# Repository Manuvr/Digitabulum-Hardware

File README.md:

# Digitabulum-Hardware

    .__       ,    .     .
    |  \* _ *-+- _.|_ . .|. .._ _
    |__/|(_]| | (_][_)(_||(_|[ | )
         ._|                      

Hardware source files for Manuvr's motion capture glove.

------------------------

## KiCAD Projects in this repo

### Production Parts

Project | Purpose
:-----|:------
Digitabulum-r2 | Sensor front-end PCB. (Pending release)
r2-Metacarpals | Flex circuit for the metacarpals. (Pending release)
r2-Digit | Flex circuit for digits. (Pending release)
[r2-Backplane](r2-Backplane) | A backplane PCB containing the power-management block and associated support circuits.
[Compute-WROOM32](Compute-WROOM32) | A digitabulum compute PCB based on Espressif's WROOM32 module.

### Hacking and Development Tools

Project | Purpose
:-----|:------
[r2-Dev-Backplane](r2-Dev-Backplane) | A backplane intended for developing CPLD images, Compute PCBs, and power management subsystems.
[PowerPlant-Module](PowerPlant-Module) | Digitabulum's power-management block implemented as a stand-alone breadboard module.
[r2-Adapter](r2-Adapter) | A debugging and development tool. It adapts a Digitabulum board to a standard breadboard. It is also useful as a template for a custom backplane.
[Compute-Template](Compute-Template) | A debugging and development tool. Provides a breakout to the compute/comm PCB connector on an r2-Backplane. It is also useful as a template for a custom Compute PCB.
[SmallTools](SmallTools) | Debugging and development tools.

------------------------

## 3D Models

Blender files for various casings and mocks can be found in the [3DModels](3DModels directory).

------------------------

## License

Manuvr's logo (our trademark) is provided indirectly for the sake of reproducing PCBs of our design, but may not be used on original work without written permission from Manuvr, Inc.

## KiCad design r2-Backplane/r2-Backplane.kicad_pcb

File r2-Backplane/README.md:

# r2-Backplane

This is a backplane PCB for Digitabulum containing the power-management block and associated support circuits.

## Intended usage

This PCB, combined with a Compute board, and a Digitabulum-r2 board (plus sensors) forms a complete electronics package for a single motion-capture glove.

The power-management block of this backplane is broken out in the [PowerPlant-Module](../PowerPlant-Module).

The CPLD GPIO pin has been routed to the 2v5/3v3 selection signal.

## Features
* ESD protection diodes for ingress-resistant USB port.
* Supports full software management of battery.
* Supports reduced-voltage operation and full power down of the sensor package for maximum battery longevity.
* JTAG breakout for in-circuit programming of CPLD.

------------------------

Front | Back
:-------:|:------:
 |

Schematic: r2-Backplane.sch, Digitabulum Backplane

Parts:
C1, C3, C7: 1uF; C_0402_NoSilk; Digikey_Number 490-1320-1-ND
C2: 4.7uF; C_0805; Digikey_Number 490-3335-1-ND
C4, C11: 22uF; C_0805; Digikey_Number 490-1719-1-ND
C5, C10: 10uF; C_0805; Digikey_Number 490-3340-1-ND
C6, C9: 10uF; C_0402_NoSilk; Digikey_Number 490-3340-1-ND
C8: 10nF; C_0402_NoSilk; Digikey_Number 399-1279-1-ND
C12: 0.1uF; C_0402_NoSilk; Digikey_Number 1276-1506-1-ND
CARY1, CARY2, CARY3, CARY4, CARY5: 100nF; CapArray_CKCL44; Digikey_Number 445-1838-1-ND
CON1: USB-MICRO-B; USB_ZX62WRD-B-5PC; Digikey_Number H12192CT-ND
D1: Charge; R_0402_NoSilk; Digikey_Number LNJ347W83RACT-ND
F1: 1A; R_0805_HandSoldering; Digikey_Number NANOSMDC075F-2CT-ND
L1, L2: 2.2uH; L-SMD; Digikey_Number 308-2294-1-ND
L3: 1uH; Neosid_Inductor_SM-NE29_SMD1008; Digikey_Number 490-6699-1-ND
P1: CONN_01X01; ManuvrLogo
P2: CONN_01X02; Pin_Header_Straight_1x02_Pitch2.54mm
P3: CONN_02X16; DF12(3.0)-32DS-0.5V(86); Digikey_Number H11708TR-ND
P4: HiRose-02X15; DF12(4.0)-30DS-0.5V(86); Digikey_Num H5238CT-ND
P6: DEBUG; Pin_Header_Straight_1x08_Pitch1.27mm
QA_NPN1: QA_NPN; SOT-363_SC-70-6_Handsoldering; Digikey_Number NC7SV57P6XCT-ND
R1, R3: 1k; R_0402_NoSilk; Digikey_Number P1.00KLCT-ND
R4: 68mOhm; R_2512; Digikey_Number CSRN2512FK68L0CT-ND
RP1: 22; RES_4_EXBN8V; Digikey_Number Y10220CT-ND
RP2: 1k; RES_4_EXBN8V; Digikey_Number Y9102CT-ND
U1, U2, U3, U4: LSF0204x; R-PUQFN-N12; Digikey_Number 296-40404-1-ND
U5: LTC2942-1; DFN-6-1EP_2x3mm_Pitch0.5mm; Digikey_Number LTC2942CDCB-1#TRMPBFCT-ND
U6: BQ24155; Digikey_Number 296-27187-1-ND
U7: SC283; MLPQ-W18 (2mmx3mm); Digikey_Number SC283WLCT-ND
U8: EMIF02-USB03F2; FCBGA12; Digikey_Number 497-13521-1-ND

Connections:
/ALERT: P4.30, U5.5
/CHIP_PU: P4.15, P6.2
/CPLD_EXT_CLK: P3.31, U3.4
/CPLD_GPIO_0: P3.21, QA_NPN1.6
/CPLD_OE: P3.26, U3.5
/I2C_SCL: P4.4, U4.9, U5.3, U6.2
/I2C_SCL_LV: P3.15, RP2.4 (R4.1), U4.3
/I2C_SDA: P4.5, U4.8, U5.4, U6.3
/I2C_SDA_LV: P3.14, RP2.3 (R3.1), U4.4
/IRQ_WAKEUP: P3.17, U2.5
/ISEL: P4.6, U6.5
/PIN_0: P4.14, P6.3
/SPI1_CLK: P3.20, U2.2
/SPI1_CS_0: P3.32, U3.3
/SPI1_MISO: P3.18, U2.4
/SPI1_MOSI: P3.19, U2.3
/SPI2_CLK: P3.24, U1.3
/SPI2_CS: P3.23, U1.4
/SPI2_MOSI: P3.22, U1.5
/TCK: P3.28, P6.5, R1.2
/TDI: P3.30, P6.7
/TDO: P3.29, P6.6
/TMS: P3.27, P6.4
/USB_D+: P4.2, RP1.7 (R2.2), U8.C3
/USB_D-: P4.1, RP1.8 (R1.2), U8.D3
/VCC0: C4.1, CARY1.5, CARY1.7, CARY2.5, CARY2.7, CARY3.5, CARY3.7, CARY4.5, CARY4.7, CARY5.1, CARY5.3, CARY5.5, CARY5.7, L1.1, P4.10, P4.11, QA_NPN1.3, QA_NPN1.5, U1.11, U2.11, U3.11, U4.11, U7.18
/VCC1: C11.1, CARY1.1, CARY1.3, CARY2.1, CARY2.3, CARY3.1, CARY3.3, CARY4.1, CARY4.3, L2.2, P3.6, P3.7, P6.8, RP2.5 (R4.2), RP2.6 (R3.2), RP2.7 (R2.2), RP2.8 (R1.2), U1.1, U2.1, U3.1, U4.1, U7.9
/VCCUSB: C1.1, C6.1, CON1.1, P4.7, R3.2, U6.14, U8.B3
/Vbatt: C5.1, C7.1, C9.1, C10.1, P3.9, P3.10, R4.1, U5.1, U6.6, U6.7, U7.1, U7.10, U7.14, U7.15, U7.16, U7.17
/Vlipo: F1.2, U5.6
/~CPLD_RESET: P3.25, U1.2
/~LED_INT: P3.13, RP2.1 (R1.1), U4.5
/~LED_RESET: P3.16, U4.2
/~REQ: P3.12, U3.2
/~SHUTDOWN: P4.13, QA_NPN1.1, U1.12, U2.12, U3.12, U4.12, U7.5, U7.7, U7.8
GND: C1.2, C2.2, C3.2, C4.2, C5.2, C6.2, C7.2, C9.2, C10.2, C11.2, C12.2, CARY1.2, CARY1.4, CARY1.6, CARY1.8, CARY2.2, CARY2.4, CARY2.6, CARY2.8, CARY3.2, CARY3.4, CARY3.6, CARY3.8, CARY4.2, CARY4.4, CARY4.6, CARY4.8, CARY5.2, CARY5.4, CARY5.6, CARY5.8, CON1.5, CON1.G0, CON1.G1, CON1.G2, CON1.G3, CON1.G4, CON1.G5, CON1.G6, P1.1, P2.1, P3.1, P3.2, P3.3, P3.4, P3.N0, P3.N1, P4.3, P4.8, P4.9, P4.12, P4.N0, P4.N1, P6.1, QA_NPN1.2, R1.1, RP1.3 (R3.1), RP1.4 (R4.1), RP1.5 (R4.2), RP1.6 (R3.2), U1.6, U2.6, U3.6, U4.6, U5.2, U6.0, U6.10, U6.11, U7.3, U7.4, U7.12, U7.13, U7.T1, U7.T2, U8.A2, U8.D2
unnamed: C2.1, U6.13
unnamed: C3.1, U6.8
unnamed: C8.1, L3.1, U6.12
unnamed: C8.2, U6.1
unnamed: C12.1, L3.2, R4.2, U6.9
unnamed: CON1.2, RP1.1 (R1.1), U8.D1
unnamed: CON1.3, RP1.2 (R2.1), U8.C1
unnamed: CON1.4, U8.A3
unnamed: D1.1 (K), U6.4
unnamed: D1.2 (A), R3.1
unnamed: F1.1, P2.2
unnamed: L1.2, U7.2
unnamed: L2.1, U7.11
unnamed: P4.16, U2.7
unnamed: P4.17, U2.8
unnamed: P4.18, U2.9
unnamed: P4.19, U2.10
unnamed: P4.20, U1.7
unnamed: P4.21, U1.8
unnamed: P4.22, U1.9
unnamed: P4.23, U1.10
unnamed: P4.24, U3.7
unnamed: P4.25, U3.8
unnamed: P4.26, U3.9
unnamed: P4.27, U3.10
unnamed: P4.28, U4.7
unnamed: P4.29, U4.10
unnamed: QA_NPN1.4, U7.6

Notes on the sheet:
We will use these CPLD faculties for power control.
NOTE: This is actually an NC7SV57. The pins and footprint are correct.
NOTE: This design assumes that the system half of the voltage regulator is always running at 3.3v.

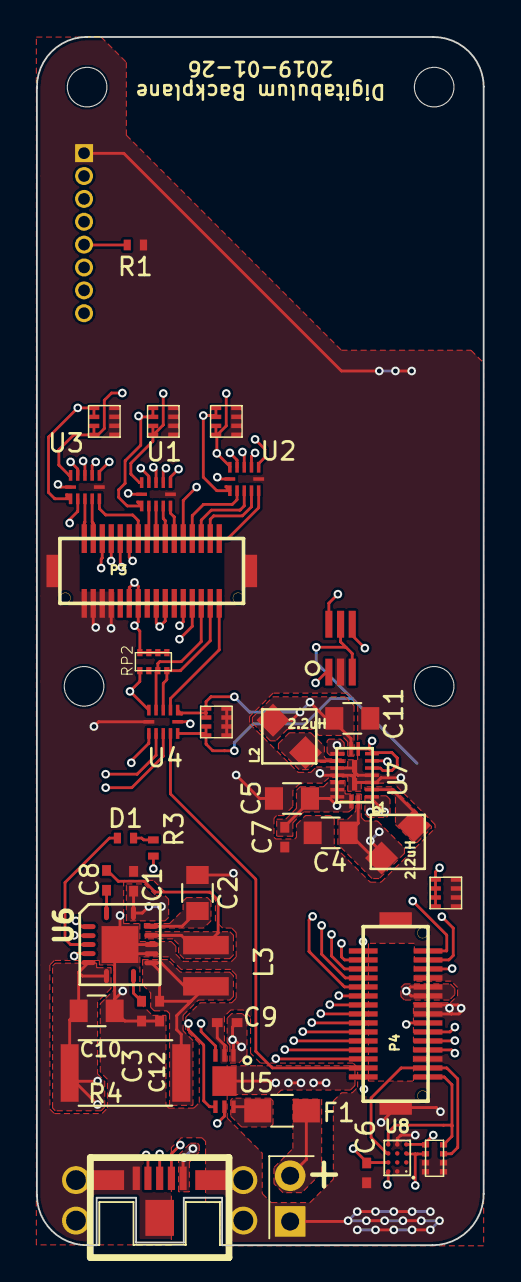
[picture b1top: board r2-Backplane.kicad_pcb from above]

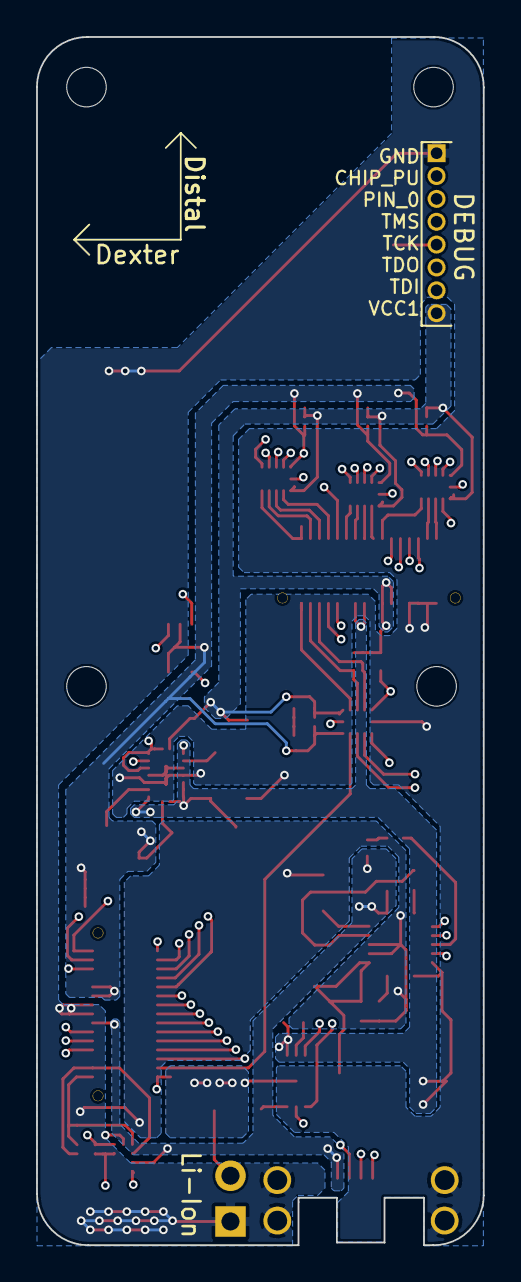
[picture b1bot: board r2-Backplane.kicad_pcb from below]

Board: 4 copper layers, 24.8 x 67.1 mm, 47 parts (2 on the bottom side), 64 nets.

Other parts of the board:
MH0: MH0; MountingHole_2.2mm_M2_DIN965
MH1: MH1; MountingHole_2.2mm_M2_DIN965
MH2, MH3: MountingHole_2.2mm_M2_DIN965
P1#2: CONN_01X01; ManuvrLogo

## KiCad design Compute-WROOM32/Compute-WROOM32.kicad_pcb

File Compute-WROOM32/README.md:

# Compute-WROOM32

This is one possible compute PCB to be used with Digitabulum-r2.

## Intended usage

This PCB, combined with a [backplane](../r2-Backplane), and a Digitabulum-r2 board (plus sensors) forms a complete electronics package for a single motion-capture glove.

## Features

* Integrated USB<-->Serial converter with Espressif monitor reset support.

## Attribution
This project uses [adamjvr's KiCAD library for the ESP32](https://github.com/adamjvr/ESP32-kiCAD-Footprints).

------------------------

Front | Back
:-------:|:------:
 |

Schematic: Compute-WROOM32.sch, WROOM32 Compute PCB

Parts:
C1: 10nF; C_0402_NoSilk; Digikey_Number 399-1279-1-ND
C2: 100uF; C_0805; Digikey_Number 478-8393-1-ND
C3: 4.7uF; C_0402_NoSilk; Digikey_Number 445-5947-1-ND
C5, C6: 0.1uF; C_0402_NoSilk; Digikey_Number 1276-1506-1-ND
CARY1, CARY3: 100nF; CapArray_CKCL44; Digikey_Number 445-1838-1-ND
CARY4: 22pF; CapArray_CKCL44; Digikey_Number 445-1824-1-ND
P1: HiRose-02X15; DF12(4.0)-30DS-0.5V(86); Digikey_Number H5215CT-ND
P4: CONN_01X01; ManuvrLogo
QA_NPN1: QA_NPN; TSOT-23-6_MK06A_HandSoldering; Digikey_Number 1727-5166-1-ND
RP1: 15k; RES_4_EXBN8V; Digikey_Number Y10153CT-ND
RP2: 15k; RES_4_EXBN8V; Digikey_Number Y9102CT-ND
U1: ESP32-WROOM_U; ESP32-WROOM-U; Digikey_Number 1904-1028-1-ND
U2: FT231XS; LFCSP_WQ20; Digikey_Number 768-1128-1-ND
U3: ASTMLP; ASTMLPD; Digikey_Number ‎535-13087-1-ND‎

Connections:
/ALERT: P1.1, U1.33
/CHIP_PU: CARY3.4, P1.16, QA_NPN1.6, RP1.6 (R3), U1.3
/CPLD_EXT_CLK: P1.6, U3.3
/CPLD_OE: P1.7, U1.26
/FTDI_RESET: C6.1, U1.36, U2.10, U2.11, U2.20
/I2C_SCL: P1.27, RP2.5 (R4), U1.12
/I2C_SDA: P1.26, RP2.6 (R3), U1.11
/IRQ_WAKEUP: P1.15, U1.8
/ISEL: P1.25, U1.37
/PIN_0: CARY3.2, P1.17, QA_NPN1.3, RP1.5 (R4), U1.25
/RxD: U1.35, U2.1
/SPI1_CLK: P1.12, U1.16
/SPI1_CS: P1.5, U1.28
/SPI1_MISO: P1.14, U1.10
/SPI1_MOSI: P1.13, U1.13
/SPI2_CLK: P1.9, U1.6
/SPI2_CS: P1.10, U1.7
/SPI2_MOSI: P1.11, U1.9
/TxD: U1.34, U2.17
/USB_D+: CARY4.2, CARY4.4, P1.29, U2.8
/USB_D-: CARY4.6, CARY4.8, P1.30, U2.9
/VCC0: C2.1, CARY1.1, CARY1.3, CARY1.5, CARY1.7, CARY3.6, CARY3.8, P1.20, P1.21, RP1.1, RP1.2, RP1.3, RP1.4, RP2.1, RP2.2, RP2.3, RP2.4, U1.2, U3.4
/VCCUSB: C1.1, C3.1, C5.1, P1.24, U2.12
/~CPLD_RESET: P1.8, U1.24
/~LED_INT: P1.3, U1.31
/~LED_RESET: P1.2, U1.29
/~REQ: P1.4, U1.30
/~SHUTDOWN: P1.18, U1.14
GND: C1.2, C2.2, C3.2, C5.2, C6.2, CARY1.2, CARY1.4, CARY1.6, CARY1.8, CARY3.1, CARY3.3, CARY3.5, CARY3.7, CARY4.1, CARY4.3, CARY4.5, CARY4.7, P1.19, P1.22, P1.23, P1.28, P1.N0, P1.N1, P4.1, U1.1, U1.15, U1.38, U1.39, U2.3, U2.13, U2.21, U3.2
unnamed: QA_NPN1.1, QA_NPN1.5, U2.19
unnamed: QA_NPN1.2, QA_NPN1.4, U2.18
unnamed: U1.27, U3.1

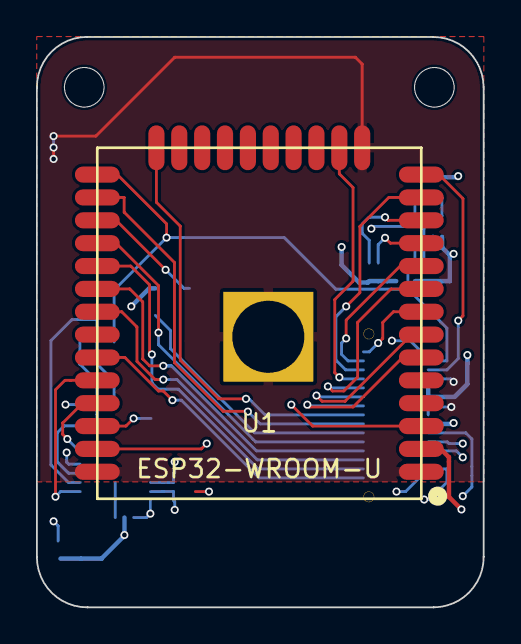
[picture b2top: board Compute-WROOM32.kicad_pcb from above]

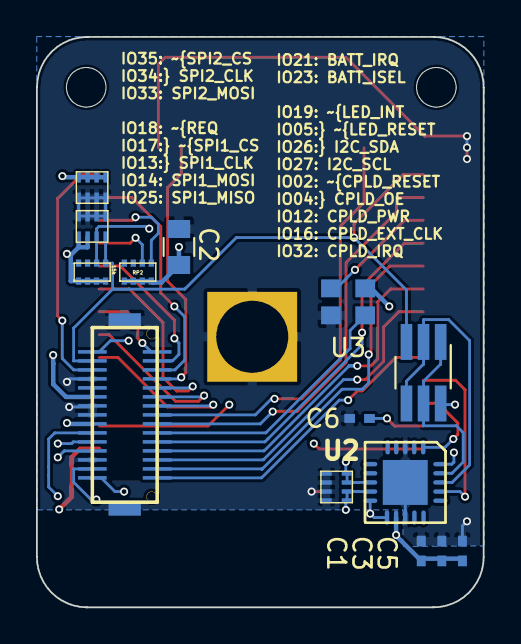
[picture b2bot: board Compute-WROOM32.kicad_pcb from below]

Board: 4 copper layers, 24.8 x 31.7 mm, 17 parts (14 on the bottom side), 32 nets.

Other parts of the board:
mh0, mh1: MountingHole_2.2mm_M2_DIN965

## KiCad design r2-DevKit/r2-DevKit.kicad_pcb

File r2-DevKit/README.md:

# r2-DevKit

This is a backplane PCB for Digitabulum. When combined with the [PowerPlant](../PowerPlant-Module), it has the same schematic as the [r2-Backplane](../r2-Backplane).

## Intended usage

This board is intended as a testing harness for functional subunits designed for use with the Digitabulum sensor package. This would be the board you would want for prototyping new CPLD designs, power supplies, or compute modules.

If you do not want to do those things, but just want a working glove, you should use the [r2-Backplane](../r2-Backplane) instead.

The CPLD GPIO pin has been routed to the 2v5/3v3 selection signal.

## Features
* ESD protection diodes for ingress-resistant USB port.
* Supports full software management of battery.
* Supports reduced-voltage operation and full power down of the sensor package for maximum battery longevity.
* JTAG breakout for in-circuit programming of CPLD.

------------------------

Front | Back
:-------:|:------:
 |

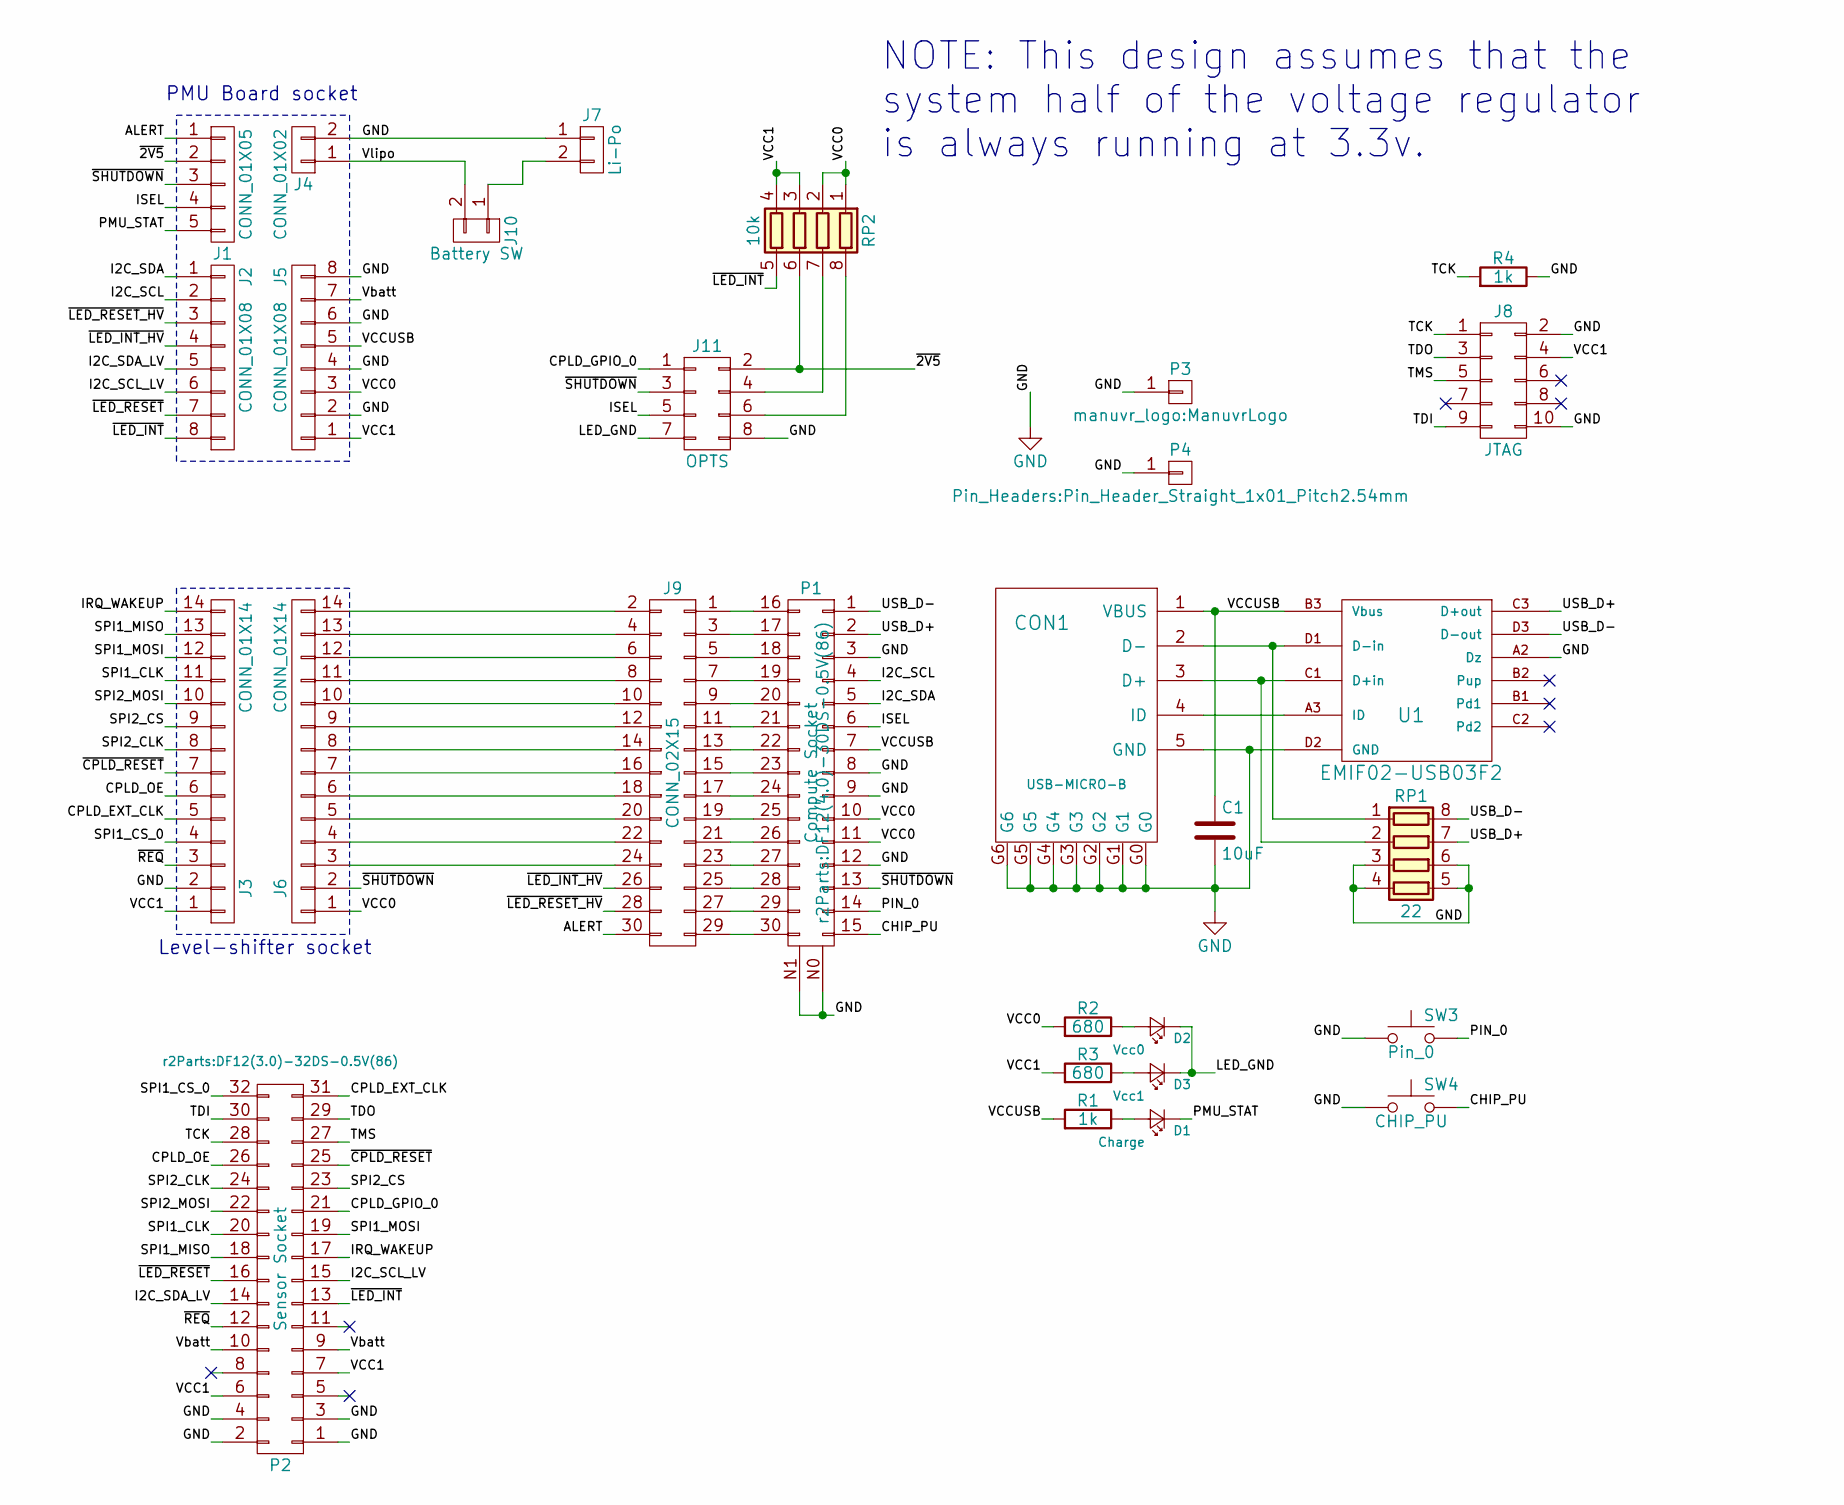
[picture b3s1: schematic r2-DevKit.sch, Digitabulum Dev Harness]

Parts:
C1: 10uF; C_0402_NoSilk; Digikey_Number 490-3340-1-ND
CON1: USB-MICRO-B; USB_ZX62WRD-B-5PC; Digikey_Number H12192CT-ND
D1: Charge; D_0603; Digikey_Number 732-4971-1-ND
D2: Vcc0; D_0603; Digikey_Number 732-4971-1-ND
D3: Vcc1; D_0603; Digikey_Number 732-4971-1-ND
J1: CONN_01X05; Pin_Header_Straight_1x05_Pitch2.54mm
J2, J5: CONN_01X08; Pin_Header_Straight_1x08_Pitch2.54mm
J3, J6: CONN_01X14; Pin_Header_Straight_1x14_Pitch2.54mm
J4: CONN_01X02; Pin_Header_Straight_1x02_Pitch2.54mm
J7: Li-Po; JST-Battery-Right-Angle; Digikey_Number 455-1749-6-ND
J8: JTAG; IDC_Header_Straight_10pins
J9: CONN_02X15; Pin_Header_Straight_2x15_Pitch2.54mm
J10: Battery SW; Pin_Header_Straight_1x02_Pitch2.54mm
J11: OPTS; Pin_Header_Straight_2x04_Pitch2.54mm
P1: Compute Socket; DF12(4.0)-30DS-0.5V(86); Digikey_Num H5238CT-ND
P2: Sensor Socket; DF12(3.0)-32DS-0.5V(86); Digikey_Number H11708TR-ND
P3: CONN_01X01; ManuvrLogo
P4: CONN_01X01; Pin_Header_Straight_1x01_Pitch2.54mm
R1, R4: 1k; R_0402_NoSilk; Digikey_Number 311-1.0KJRCT-ND
R2, R3: 680; R_0402_NoSilk; Digikey_Number 311-680JRCT-ND
RP1: 22; RES_4_EXBN8V; Digikey_Number Y10220CT-ND
RP2: 10k; RES_4_EXBN8V; Digikey_Number Y10220CT-ND
SW3: Pin_0; SW_SPST_Panasonic_EVQPL_3PL_5PL_PT_A15
SW4: CHIP_PU; SW_SPST_Panasonic_EVQPL_3PL_5PL_PT_A15
U1: EMIF02-USB03F2; FCBGA12; Digikey_Number 497-13521-1-ND

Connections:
/ALERT: J1.1, J9.30
/CHIP_PU: P1.15, SW4.2
/CPLD_EXT_CLK: J3.5, P2.31
/CPLD_GPIO_0: J11.1, P2.21
/CPLD_OE: J3.6, P2.26
/I2C_SCL: J2.2, P1.4
/I2C_SCL_LV: J2.6, P2.15
/I2C_SDA: J2.1, P1.5
/I2C_SDA_LV: J2.5, P2.14
/IRQ_WAKEUP: J3.14, P2.17
/ISEL: J1.4, J11.5, P1.6
/LED_GND: D2.1 (K), D3.1 (K), J11.7
/PIN_0: P1.14, SW3.2
/PMU_STAT: D1.1 (K), J1.5
/SPI1_CLK: J3.11, P2.20
/SPI1_CS_0: J3.4, P2.32
/SPI1_MISO: J3.13, P2.18
/SPI1_MOSI: J3.12, P2.19
/SPI2_CLK: J3.8, P2.24
/SPI2_CS: J3.9, P2.23
/SPI2_MOSI: J3.10, P2.22
/TCK: J8.1, P2.28, R4.2
/TDI: J8.9, P2.30
/TDO: J8.3, P2.29
/TMS: J8.5, P2.27
/USB_D+: P1.2, RP1.7 (R2.2), U1.C3 (D+out)
/USB_D-: P1.1, RP1.8 (R1.2), U1.D3 (D-out)
/VCC0: J5.3, J6.1, P1.10, P1.11, R2.2, RP2.1 (R1.1), RP2.2 (R2.1)
/VCC1: J3.1, J5.1, J8.4, P2.6, P2.7, R3.2, RP2.3 (R3.1), RP2.4 (R4.1)
/VCCUSB: C1.1, CON1.1 (VBUS), J5.5, P1.7, R1.2, U1.B3 (Vbus)
/Vbatt: J5.7, P2.9, P2.10
/Vlipo: J4.1, J10.2
/~2V5: J1.2, J11.2, RP2.6 (R3.2)
/~CPLD_RESET: J3.7, P2.25
/~LED_INT: J2.8, P2.13, RP2.5 (R4.2)
/~LED_INT_HV: J2.4, J9.26
/~LED_RESET: J2.7, P2.16
/~LED_RESET_HV: J2.3, J9.28
/~REQ: J3.3, P2.12
/~SHUTDOWN: J1.3, J6.2, J11.3, P1.13
GND: C1.2, CON1.5 (GND), CON1.G0, CON1.G1, CON1.G2, CON1.G3, CON1.G4, CON1.G5, CON1.G6, J3.2, J4.2, J5.2, J5.4, J5.6, J5.8, J7.1, J8.2, J8.10, J11.8, P1.3, P1.8, P1.9, P1.12, P1.N0, P1.N1, P2.1, P2.2, P2.3, P2.4, P3.1, P4.1, R4.1, RP1.3 (R3.1), RP1.4 (R4.1), RP1.5 (R4.2), RP1.6 (R3.2), SW3.1, SW4.1, U1.A2 (Dz), U1.D2 (GND)
unnamed: CON1.2 (D-), RP1.1 (R1.1), U1.D1 (D-in)
unnamed: CON1.3 (D+), RP1.2 (R2.1), U1.C1 (D+in)
unnamed: CON1.4 (ID), U1.A3 (ID)
unnamed: D1.2 (A), R1.1
unnamed: D2.2 (A), R2.1
unnamed: D3.2 (A), R3.1
unnamed: J6.3, J9.24
unnamed: J6.4, J9.22
unnamed: J6.5, J9.20
unnamed: J6.6, J9.18
unnamed: J6.7, J9.16
unnamed: J6.8, J9.14
unnamed: J6.9, J9.12
unnamed: J6.10, J9.10
unnamed: J6.11, J9.8
unnamed: J6.12, J9.6
unnamed: J6.13, J9.4
unnamed: J6.14, J9.2
unnamed: J9.1, P1.16
unnamed: J9.3, P1.17
unnamed: J9.5, P1.18
unnamed: J9.7, P1.19
unnamed: J9.9, P1.20
unnamed: J9.11, P1.21
unnamed: J9.13, P1.22
unnamed: J9.15, P1.23
unnamed: J9.17, P1.24
unnamed: J9.19, P1.25
unnamed: J9.21, P1.26
unnamed: J9.23, P1.27
unnamed: J9.25, P1.28
unnamed: J9.27, P1.29
unnamed: J9.29, P1.30
unnamed: J7.2, J10.1
unnamed: J11.4, RP2.7 (R2.2)
unnamed: J11.6, RP2.8 (R1.2)

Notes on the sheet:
PMU Board socket
Level-shifter socket
NOTE: This design assumes that the system half of the voltage regulator is always running at 3.3v.

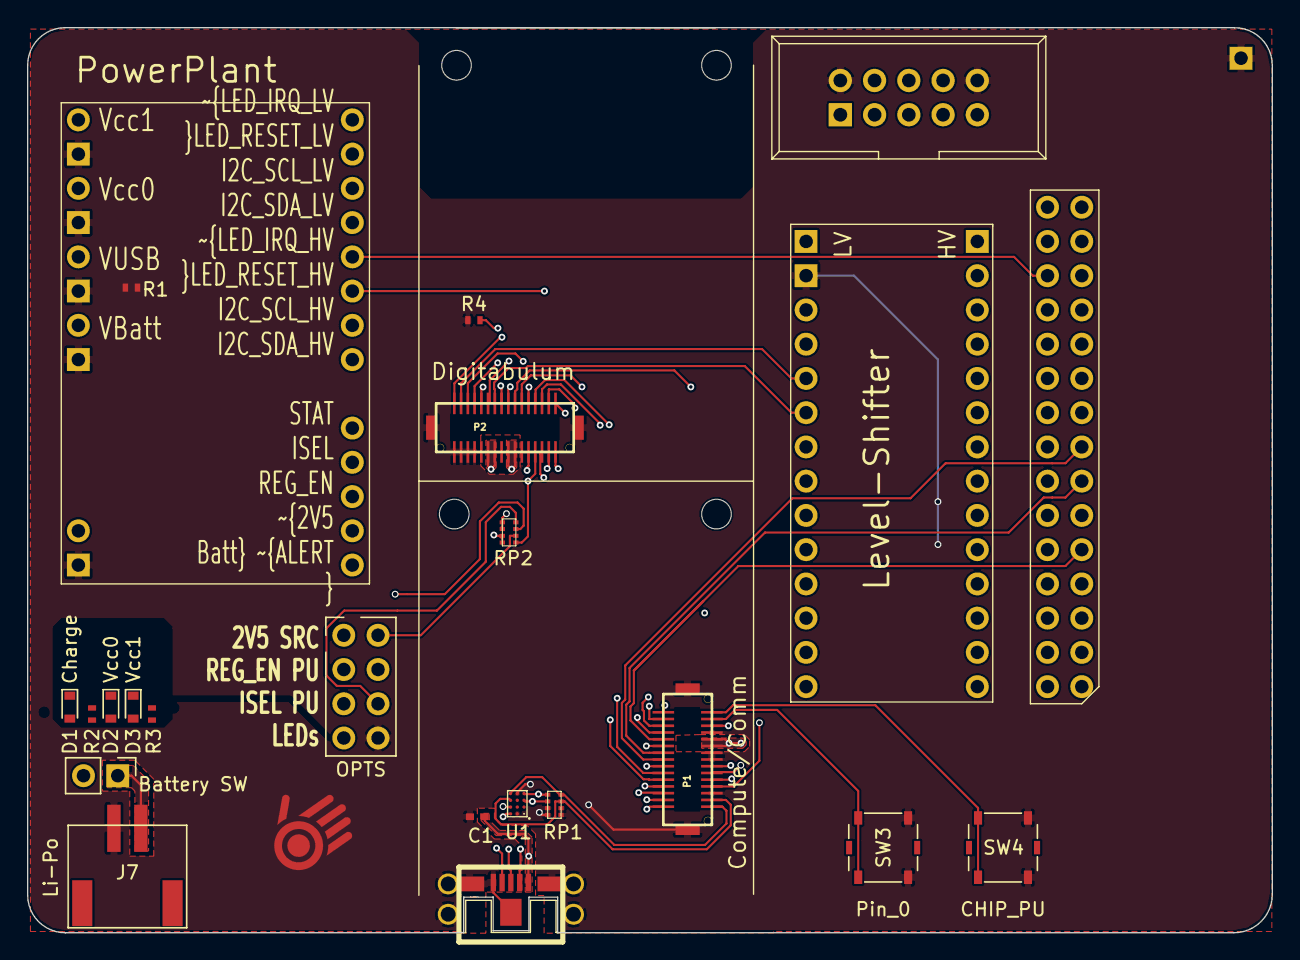
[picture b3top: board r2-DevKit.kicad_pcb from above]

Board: 4 copper layers, 92.3 x 67.1 mm, 33 parts (0 on the bottom side), 77 nets.

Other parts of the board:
MH0: MH0; MountingHole_2.2mm_M2_DIN965
MH1: MH1; MountingHole_2.2mm_M2_DIN965
MH2, MH3: MountingHole_2.2mm_M2_DIN965

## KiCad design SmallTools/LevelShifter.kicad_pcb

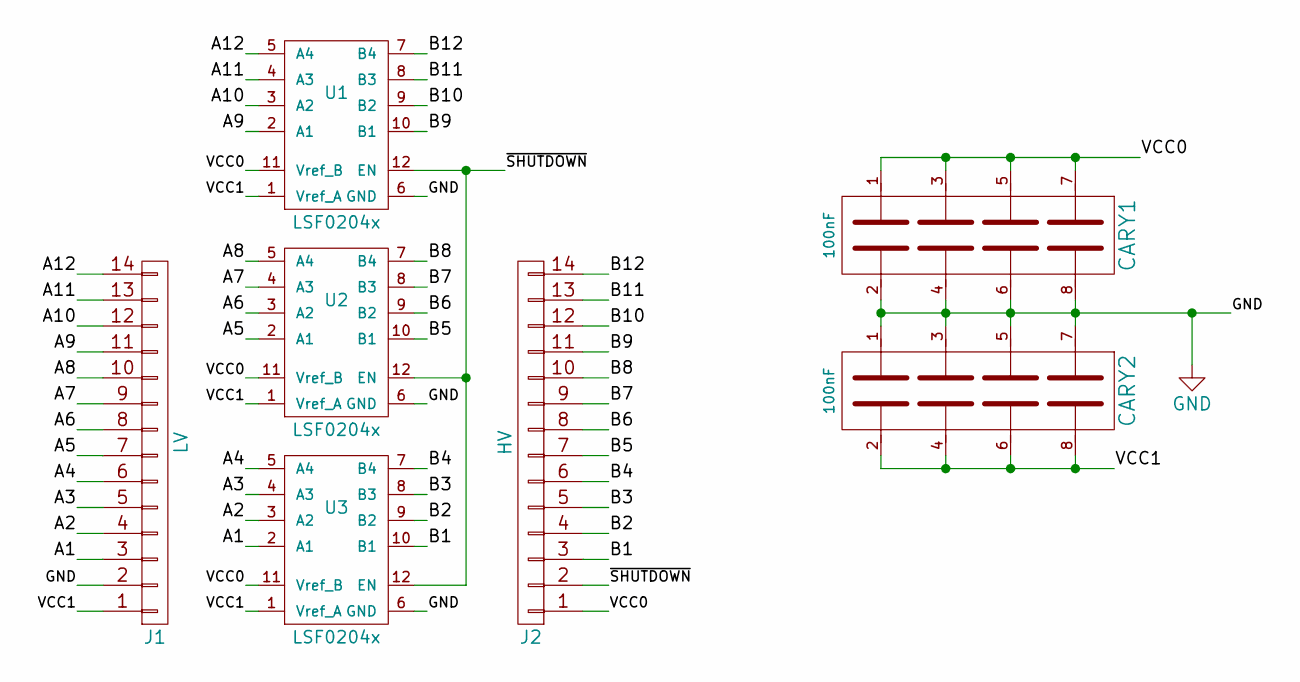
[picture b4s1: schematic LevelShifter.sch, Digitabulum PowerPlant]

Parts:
CARY1, CARY2: 100nF; CapArray_CKCL44; Digikey_Number 445-1838-1-ND
J1: LV; Pin_Header_Straight_1x14_Pitch2.54mm
J2: HV; Pin_Header_Straight_1x14_Pitch2.54mm
U1, U2, U3: LSF0204x; R-PUQFN-N12

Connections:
/A1: J1.3, U3.2 (A1)
/A2: J1.4, U3.3 (A2)
/A3: J1.5, U3.4 (A3)
/A4: J1.6, U3.5 (A4)
/A5: J1.7, U2.2 (A1)
/A6: J1.8, U2.3 (A2)
/A7: J1.9, U2.4 (A3)
/A8: J1.10, U2.5 (A4)
/A9: J1.11, U1.2 (A1)
/A10: J1.12, U1.3 (A2)
/A11: J1.13, U1.4 (A3)
/A12: J1.14, U1.5 (A4)
/B1: J2.3, U3.10 (B1)
/B2: J2.4, U3.9 (B2)
/B3: J2.5, U3.8 (B3)
/B4: J2.6, U3.7 (B4)
/B5: J2.7, U2.10 (B1)
/B6: J2.8, U2.9 (B2)
/B7: J2.9, U2.8 (B3)
/B8: J2.10, U2.7 (B4)
/B9: J2.11, U1.10 (B1)
/B10: J2.12, U1.9 (B2)
/B11: J2.13, U1.8 (B3)
/B12: J2.14, U1.7 (B4)
/VCC0: CARY1.1, CARY1.3, CARY1.5, CARY1.7, J2.1, U1.11 (Vref_B), U2.11 (Vref_B), U3.11 (Vref_B)
/VCC1: CARY2.2, CARY2.4, CARY2.6, CARY2.8, J1.1, U1.1 (Vref_A), U2.1 (Vref_A), U3.1 (Vref_A)
/~SHUTDOWN: J2.2, U1.12 (EN), U2.12 (EN), U3.12 (EN)
GND: CARY1.2, CARY1.4, CARY1.6, CARY1.8, CARY2.1, CARY2.3, CARY2.5, CARY2.7, J1.2, U1.6 (GND), U2.6 (GND), U3.6 (GND)

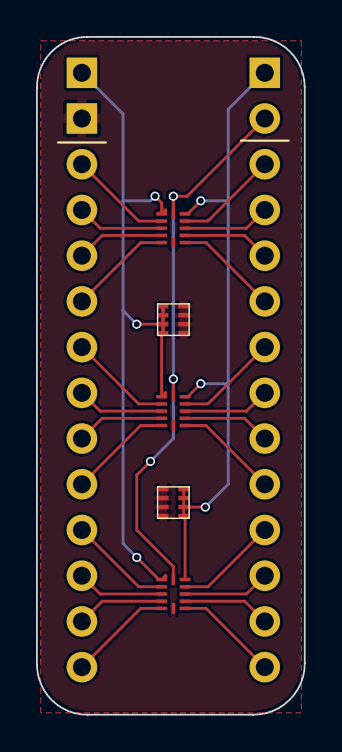
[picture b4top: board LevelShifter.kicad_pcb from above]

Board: 4 copper layers, 14.9 x 37.7 mm, 7 parts (0 on the bottom side), 28 nets.

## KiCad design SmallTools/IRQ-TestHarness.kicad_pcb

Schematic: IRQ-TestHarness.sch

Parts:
CARY1: CAPARRAY_4; CapArray_CKCL44
P1: CONN_01X05; Pin_Header_Straight_1x05_Pitch2.54mm
P2: CONN_01X05; Pin_Header_Straight_1x05_Pitch1.27mm
RP1, RP2, RP3, RP5: R_PACK4; RES_4_EXBN8V
RP4: R_PACK4; SW_DIP_x4_W5.08mm_Slide_Copal_CHS-A
SW1, SW2, SW3, SW4, SW5, SW6, SW7, SW8, SW9, SW10, SW11, SW12: SW_PUSH_SMALL_H; SW_SPST_Panasonic_EVQPL_3PL_5PL_PT_A15
U2, U3: 74HC165; DHVQFN16-3.5x2.5; Digikey_Number 568-7724-1-ND

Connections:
/GND: CARY1.2, CARY1.4, CARY1.6, CARY1.8, P1.1, P2.1, RP1.5, RP1.6, RP1.7, RP1.8, RP2.5, RP2.6, RP2.7, RP2.8, RP3.5, RP3.6, RP3.7, RP3.8, RP5.1, RP5.2, RP5.3, RP5.4, U2.0, U2.8, U2.10, U2.15, U3.0, U3.8, U3.15
/INT_0_0: RP3.1, SW9.1, U3.3
/INT_0_1: RP2.1, SW5.1, U2.3
/INT_0_2: RP1.4, SW4.1, U2.14
/INT_1_0: RP3.2, SW10.1, U3.4
/INT_1_1: RP2.2, SW6.1, U2.4
/INT_1_2: RP1.3, SW3.1, U2.13
/INT_2_0: RP3.3, SW11.1, U3.5
/INT_2_1: RP2.3, SW7.1, U2.5
/INT_2_2: RP1.2, SW2.1, U2.12
/INT_3_0: RP3.4, SW12.1, U3.6
/INT_3_1: RP2.4, SW8.1, U2.6
/INT_3_2: RP1.1, SW1.1, U2.11
/IRQ_CLK: P1.2, P2.2, U2.2, U3.2
/IRQ_DAT: P1.4, P2.4, U3.9
/IRQ_LOAD: P1.3, P2.3, U2.1, U3.1
/VCC: CARY1.1, CARY1.3, CARY1.5, CARY1.7, P1.5, P2.5, RP4.1, RP4.2, RP4.3, RP4.4, SW1.2, SW2.2, SW3.2, SW4.2, SW5.2, SW6.2, SW7.2, SW8.2, SW9.2, SW10.2, SW11.2, SW12.2, U2.16, U3.16
unnamed: RP4.5, RP5.8, U3.11
unnamed: RP4.6, RP5.7, U3.12
unnamed: RP4.7, RP5.6, U3.13
unnamed: RP4.8, RP5.5, U3.14
unnamed: U2.9, U3.10

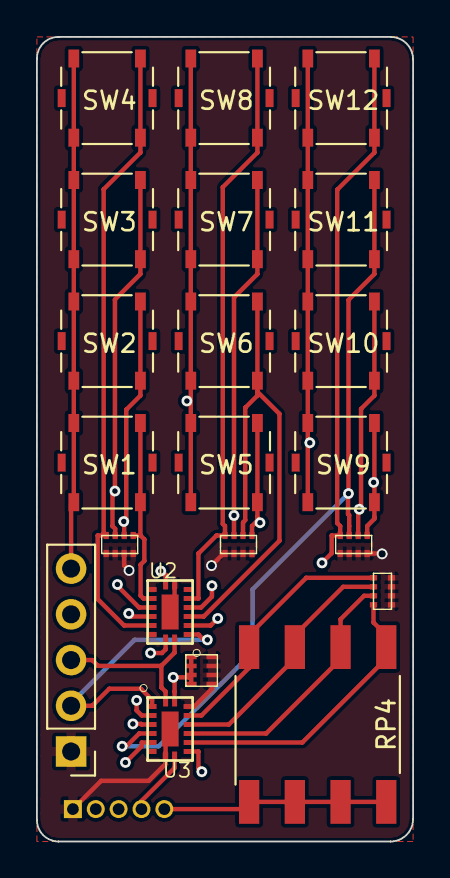
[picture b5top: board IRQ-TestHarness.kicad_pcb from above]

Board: 4 copper layers, 20.9 x 44.7 mm, 22 parts (0 on the bottom side), 22 nets.

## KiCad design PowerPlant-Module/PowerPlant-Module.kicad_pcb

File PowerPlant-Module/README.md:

# Digitabulum-PowerPlant

This is the power-management block of Manuvr's motion-capture glove. It has been broken out as a module for testing and re-use.

## Intended usage
A software-mediated single-cell li-ion battery manager for cases needing bursts of a few watts and supporting long periods of quiescent standby.

## Features
* Dual output
* Secondary regulator has three voltages (0, 2.5, 3.3), and can be changed dynamically.
* Fused battery (resetable)
* Charger and fuel gauge are both i2c
* Integrated 4-bit level-shifter (i2c capable)
* Accepts up to 20v input
* 2.54 headers
* Single-sided assembly for easy thermal-relief

## Primary components

Feature | Manufacturer | Part
:----|-----:|:----
Battery charger | TI | BQ24155
Fuel gauge | Linear | LTC2942-1
Regulator | SEMTECH | SC283
Level-shifter | TI | LSF0204

## Constraints
* Battery must be li-ion chemistry.
* Primary regulator is always on and fixed at a 3.3v output.
* No single regulator may provide more than 1.8A, and the module's maximum output wattage is 4.2 watts. See below.

Charge and discharge rate on the battery must not exceed 1A, or the internal sense resistor in the fuel gauge will burn out. There is a resetable fuse to prevent damage, but this forms the limit on the module's practical output rating. However, the charger IC can handle up to a 20v input, and could conceivably draw more than the module's maximum output from the input source as it charges and powers the load. Fuse accordingly. :-)

------------------------

Front | Back
:-------:|:------:
  |

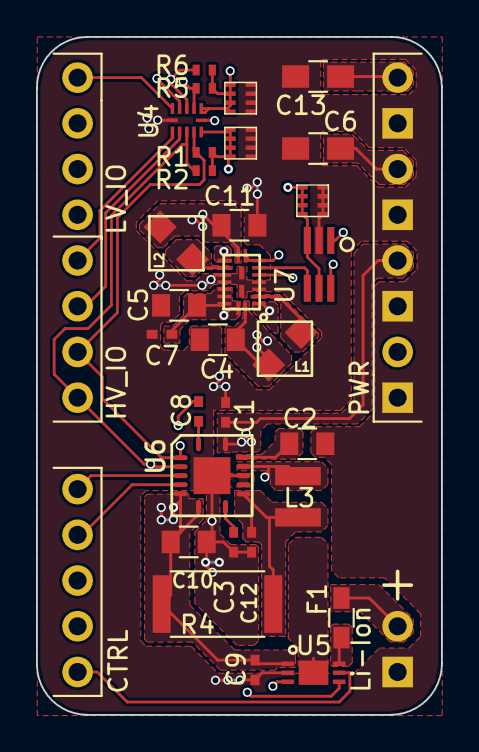
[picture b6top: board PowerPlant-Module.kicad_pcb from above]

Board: 4 copper layers, 22.5 x 37.7 mm, 35 parts (0 on the bottom side), 28 nets.

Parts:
C1, C3, C7: 1uF; C_0402_NoSilk
C2: 4.7uF; C_0805
C4, C11: 22uF; C_0805
C5, C10: 10uF; C_0805
C6, C13: 100uF; C_0805_HandSoldering
C8: 10nF; C_0402_NoSilk
C9: 10uF; C_0402_NoSilk
C12: 0.1uF; C_0402_NoSilk
CARY1, CARY2, CARY3: 100nF; CapArray_CKCL44
F1: F_Small; R_0603_HandSoldering
L1, L2: 2.2uH; L-SMD
L3: 1uH; Neosid_Inductor_SM-NE29_SMD1008
P2: CONN_01X02; Pin_Header_Straight_1x02_Pitch2.54mm
P3: PWR; Pin_Header_Straight_1x08_Pitch2.54mm
P4: CTRL; Pin_Header_Straight_1x05_Pitch2.54mm
P5: LV_IO; Pin_Header_Straight_1x04_Pitch2.54mm
P6: HV_IO; Pin_Header_Straight_1x04_Pitch2.54mm
QA_NPN1: QA_NPN; SOT-363_SC-70-6_Handsoldering
R1, R2, R5, R6: 1k; R_0402_NoSilk
R4: 68mOhm; R_2512
U4: LSF0204x; R-PUQFN-N12
U5: LTC2942-1; DFN-6-1EP_2x3mm_Pitch0.5mm
U6: BQ24155
U7: SC283; MLPQ-W18 (2mmx3mm)

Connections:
/ALERT: P4.5, U5.5
/I2C_SCL: P6.3, R1.1, U4.10, U5.3, U6.2
/I2C_SCL_LV: P5.3, R5.1, U4.2
/I2C_SDA: P6.4, R2.1, U4.9, U5.4, U6.3
/I2C_SDA_LV: P5.4, R6.1, U4.3
/IO_0: P6.1, U4.7
/IO_1: P6.2, U4.8
/ISEL: P4.2, U6.5
/LV_IO_0: P5.1, U4.5
/LV_IO_1: P5.2, U4.4
/STAT: P4.1, U6.4
/VCC0: C4.1, C6.1, CARY1.1, CARY1.3, CARY1.5, CARY1.7, CARY3.1, CARY3.3, CARY3.5, CARY3.7, L1.1, P3.6, QA_NPN1.3, QA_NPN1.5, R1.2, R2.2, U4.11, U7.18
/VCC1: C11.1, C13.1, CARY2.1, CARY2.3, CARY2.5, CARY2.7, L2.2, P3.8, R5.2, R6.2, U4.1, U7.9
/VCCUSB: C1.1, P3.4, U6.14
/Vbatt: C5.1, C7.1, C9.1, C10.1, P3.2, R4.1, U5.1, U6.6, U6.7, U7.1, U7.10, U7.14, U7.15, U7.16, U7.17
/Vlipo: F1.1, U5.6
/~2V5: P4.4, QA_NPN1.6
/~SHUTDOWN: P4.3, QA_NPN1.1, U4.12, U7.5, U7.7, U7.8
GND: C1.2, C2.2, C3.2, C4.2, C5.2, C6.2, C7.2, C9.2, C10.2, C11.2, C12.2, C13.2, CARY1.2, CARY1.4, CARY1.6, CARY1.8, CARY2.2, CARY2.4, CARY2.6, CARY2.8, CARY3.2, CARY3.4, CARY3.6, CARY3.8, P2.1, P3.1, P3.3, P3.5, P3.7, QA_NPN1.2, U4.6, U5.2, U6.0, U6.10, U6.11, U7.3, U7.4, U7.12, U7.13, U7.T1, U7.T2
unnamed: C2.1, U6.13
unnamed: C3.1, U6.8
unnamed: C8.1, L3.1, U6.12
unnamed: C8.2, U6.1
unnamed: C12.1, L3.2, R4.2, U6.9
unnamed: F1.2, P2.2
unnamed: L1.2, U7.2
unnamed: L2.1, U7.11
unnamed: QA_NPN1.4, U7.6

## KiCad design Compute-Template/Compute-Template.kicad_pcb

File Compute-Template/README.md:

# Compute-Template

Provides a breakout to the compute/comm PCB connector on the r2-Backplane. It is also useful as a template for a custom Compute PCB.

## Intended usage

This project has two purposes:

 1) To be used as-is as a signal breakout for using Digitabulum _and_ the r2-Backplane with a new microcontroller without rolling a PCB for it.

 2) To be used as a template for a custom compute PCB to be attached to the r2-Backplane.

------------------------

Front | Back
:-------:|:------:
 |

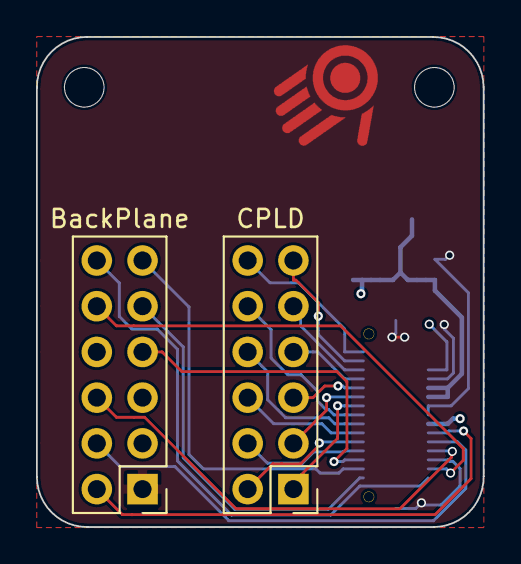
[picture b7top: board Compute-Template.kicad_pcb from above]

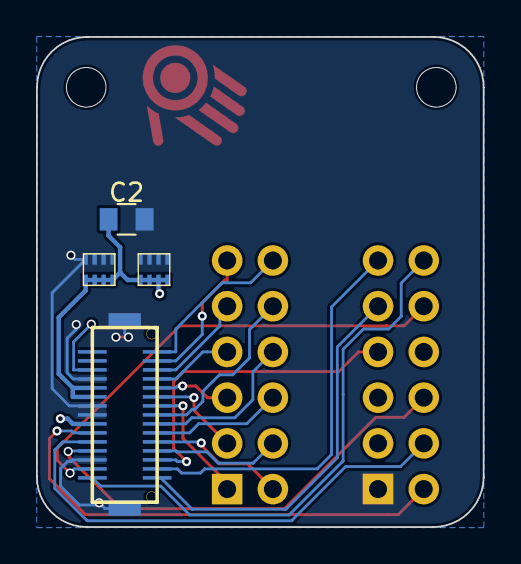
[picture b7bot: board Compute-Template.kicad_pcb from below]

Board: 4 copper layers, 24.8 x 27.2 mm, 9 parts (4 on the bottom side), 24 nets.

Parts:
C2: IANS_CAP_POLARIZED; C_0805
CARY1, CARY2: 100nF; CapArray_CKCL44
P1: HiRose-02X15; DF12(4.0)-30DS-0.5V(86)
P2: CPLD; Pin_Header_Straight_2x06_Pitch2.54mm
P3: BackPlane; Pin_Header_Straight_2x06_Pitch2.54mm
P4: CONN_01X01; ManuvrLogo
mh0, mh1: MountingHole_2.2mm_M2_DIN965

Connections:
/ALERT: P1.1, P3.9
/CPLD_EXT_CLK: P1.6, P2.6
/CPLD_OE: P1.7, P2.8
/I2C_SCL: P1.27, P3.6
/I2C_SDA: P1.26, P3.4
/IRQ_WAKEUP: P1.15, P2.12
/ISEL: P1.25, P3.2
/SPI1_CLK: P1.12, P2.7
/SPI1_CS: P1.5, P2.2
/SPI1_MISO: P1.14, P2.11
/SPI1_MOSI: P1.13, P2.9
/SPI2_CLK: P1.9, P2.1
/SPI2_CS: P1.10, P2.3
/SPI2_MOSI: P1.11, P2.5
/USB_D+: P1.29, P3.10
/USB_D-: P1.30, P3.12
/VCC0: C2.1, CARY1.1, CARY1.3, CARY1.5, CARY1.7, CARY2.1, CARY2.3, CARY2.5, CARY2.7, P1.20, P1.21, P3.5
/VCCUSB: P1.24, P3.3
/~CPLD_RESET: P1.8, P2.10
/~LED_INT: P1.3, P3.7
/~LED_RESET: P1.2, P3.11
/~REQ: P1.4, P2.4
/~SHUTDOWN: P1.18, P3.8
GND: C2.2, CARY1.2, CARY1.4, CARY1.6, CARY1.8, CARY2.2, CARY2.4, CARY2.6, CARY2.8, P1.19, P1.22, P1.23, P1.28, P1.N0, P1.N1, P3.1

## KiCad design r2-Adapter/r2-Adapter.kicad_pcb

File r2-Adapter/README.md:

# r2-Adapter

This is a breadboard adapter for Digitabulum-r2. All signals are broken out and labeled.

## Intended usage

This project has two purposes:

 1) To be used as-is as a breadboard adapter and development tool.

 2) To be used as a template for a custom Digitabulum backplane.

## Features
* JTAG breakout
* 2.54 headers

------------------------

Front | Back
:-------:|:------:
 |

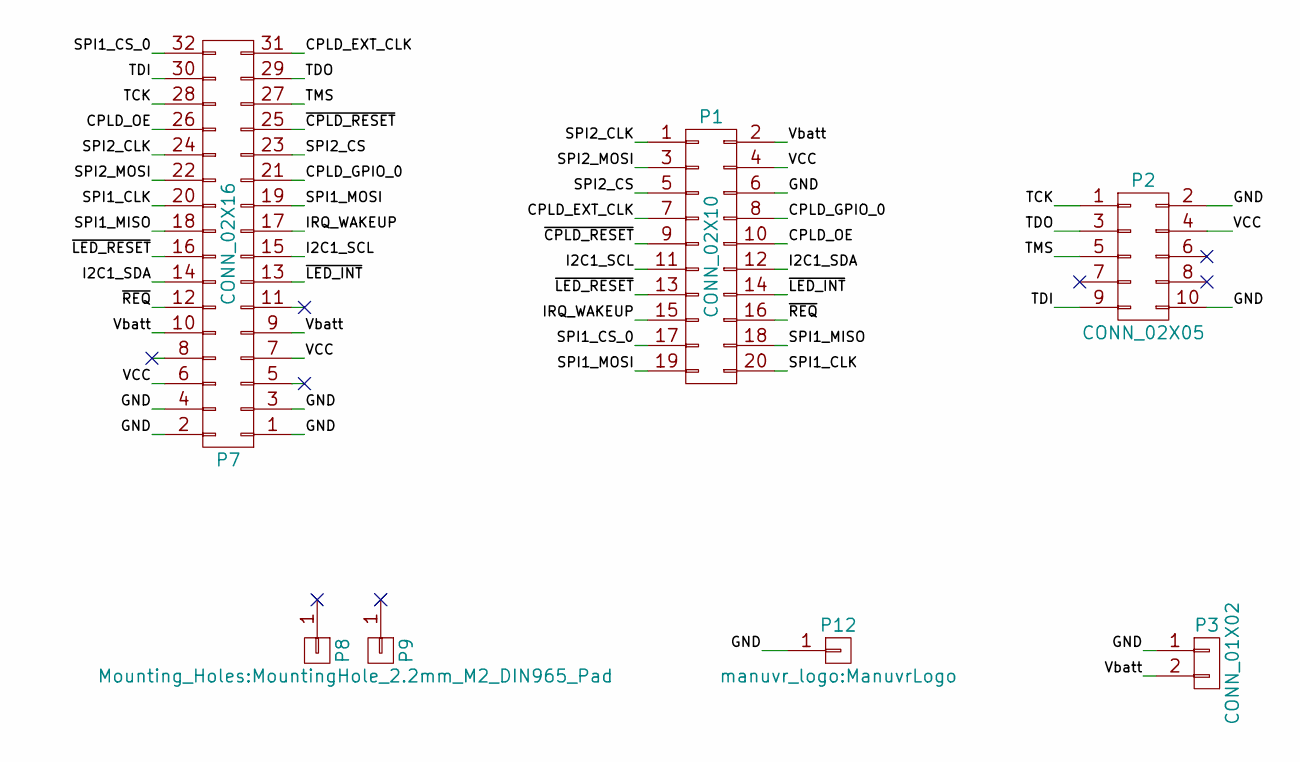
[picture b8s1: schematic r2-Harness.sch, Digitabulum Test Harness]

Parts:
P1: CONN_02X10; DIP-24_W15.24mm_Socket_LongPads
P2: CONN_02X05; Pin_Header_Angled_2x05_Pitch2.54mm
P3: CONN_01X02; Pin_Header_Straight_1x02_Pitch2.54mm
P7: CONN_02X16; DF12(3.0)-32DS-0.5V(86); Digikey_Number H5205CT-ND
P8, P9: HOLE; MountingHole_2.2mm_M2_DIN965_Pad
P12: CONN_01X01; ManuvrLogo

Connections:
/CPLD_EXT_CLK: P1.7, P7.31
/CPLD_GPIO_0: P1.8, P7.21
/CPLD_OE: P1.10, P7.26
/GND: P1.6, P2.2, P2.10, P3.1, P7.1, P7.2, P7.3, P7.4, P12.1
/I2C1_SCL: P1.11, P7.15
/I2C1_SDA: P1.12, P7.14
/IRQ_WAKEUP: P1.15, P7.17
/SPI1_CLK: P1.20, P7.20
/SPI1_CS_0: P1.17, P7.32
/SPI1_MISO: P1.18, P7.18
/SPI1_MOSI: P1.19, P7.19
/SPI2_CLK: P1.1, P7.24
/SPI2_CS: P1.5, P7.23
/SPI2_MOSI: P1.3, P7.22
/TCK: P2.1, P7.28
/TDI: P2.9, P7.30
/TDO: P2.3, P7.29
/TMS: P2.5, P7.27
/VCC: P1.4, P2.4, P7.6, P7.7
/Vbatt: P1.2, P3.2, P7.9, P7.10
/~CPLD_RESET: P1.9, P7.25
/~LED_INT: P1.14, P7.13
/~LED_RESET: P1.13, P7.16
/~REQ: P1.16, P7.12
